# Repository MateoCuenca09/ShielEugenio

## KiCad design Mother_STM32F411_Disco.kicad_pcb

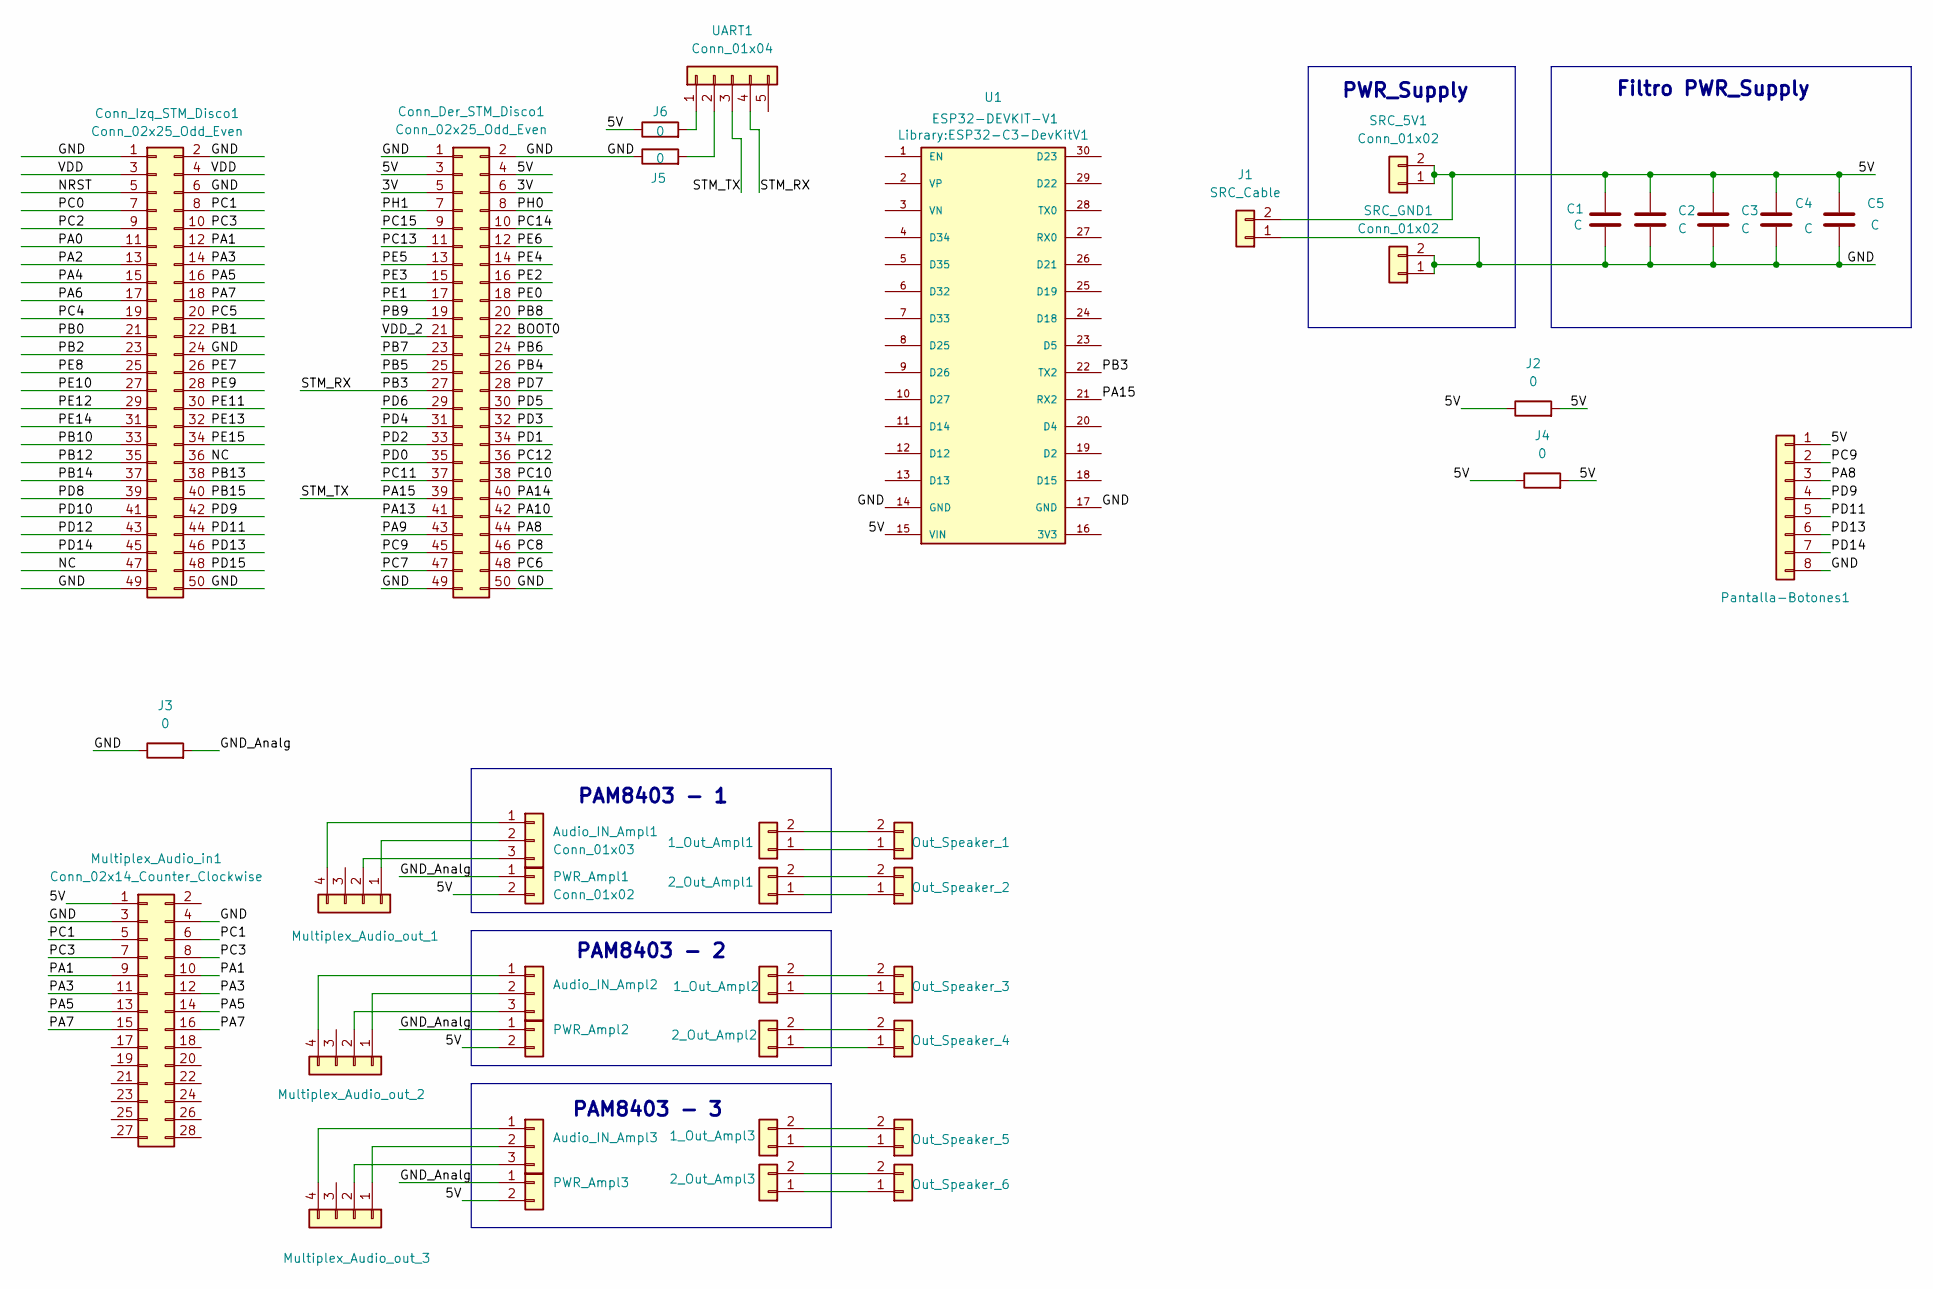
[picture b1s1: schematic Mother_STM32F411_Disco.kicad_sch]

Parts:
1_Out_Ampl1, 1_Out_Ampl2, 1_Out_Ampl3, 2_Out_Ampl1, 2_Out_Ampl2, 2_Out_Ampl3: Conn_01x02; PinSocket_1x02_P2.54mm_Vertical
Audio_IN_Ampl1, Audio_IN_Ampl2, Audio_IN_Ampl3: Conn_01x03; PinSocket_1x03_P2.54mm_Vertical
C1, C5: C; CP_Radial_D13.0mm_P5.00mm
C2, C3, C4: C; C_Disc_D8.0mm_W5.0mm_P5.00mm
Conn_Der_STM_Disco1: Conn_02x25_Odd_Even; PinSocket_2x25_P2.54mm_Vertical
Conn_Izq_STM_Disco1: Conn_02x25_Odd_Even; PinSocket_2x25_P2.54mm_Vertical
J1: SRC_Cable; TerminalBlock_Phoenix_MKDS-1,5-2_1x02_P5.00mm_Horizontal
J2, J3, J4, J5, J6: 0; R_1210_3225Metric_Pad1.30x2.65mm_HandSolder
Multiplex_Audio_in1: Conn_02x14_Counter_Clockwise; PinHeader_2x14_P2.54mm_Vertical
Multiplex_Audio_out_1, Multiplex_Audio_out_2, Multiplex_Audio_out_3: Conn_01x04; PinSocket_1x04_P2.54mm_Vertical
Out_Speaker_1, Out_Speaker_2, Out_Speaker_3, Out_Speaker_4, Out_Speaker_5, Out_Speaker_6: Conn_01x02; PinHeader_1x02_P2.54mm_Horizontal
PWR_Ampl1, PWR_Ampl2, PWR_Ampl3: Conn_01x02; PinSocket_1x02_P2.54mm_Vertical
Pantalla-Botones1: Conn_01x08; PinHeader_1x08_P2.54mm_Horizontal
SRC_5V1: Conn_01x02; PinSocket_1x02_P2.54mm_Vertical
SRC_GND1: Conn_01x02; PinSocket_1x02_P2.54mm_Vertical
U1: ESP32-DEVKIT-V1; ESP32-C3-DevKitV1; PARTREV N/A
UART1: Conn_01x04; PinHeader_1x05_P2.54mm_Horizontal

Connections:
/3V: Conn_Der_STM_Disco1.5, Conn_Der_STM_Disco1.6
/5V: C1.1, C2.1, C3.1, C4.1, C5.1, Conn_Der_STM_Disco1.3, Conn_Der_STM_Disco1.4, J1.2, J2.1, J2.2, J4.1, J4.2, J6.1, J6.2, Multiplex_Audio_in1.1, PWR_Ampl1.2, PWR_Ampl2.2, PWR_Ampl3.2, Pantalla-Botones1.1, SRC_5V1.1, SRC_5V1.2, U1.15 (VIN), UART1.1
/BOOT0: Conn_Der_STM_Disco1.22
/GND: C1.2, C2.2, C3.2, C4.2, C5.2, Conn_Der_STM_Disco1.1, Conn_Der_STM_Disco1.2, Conn_Der_STM_Disco1.49, Conn_Der_STM_Disco1.50, Conn_Izq_STM_Disco1.1, Conn_Izq_STM_Disco1.2, Conn_Izq_STM_Disco1.6, Conn_Izq_STM_Disco1.24, Conn_Izq_STM_Disco1.49, Conn_Izq_STM_Disco1.50, J1.1, J3.1, J5.1, Multiplex_Audio_in1.3, Multiplex_Audio_in1.4, Pantalla-Botones1.8, SRC_GND1.1, SRC_GND1.2, U1.14 (GND), U1.17 (GND)
/GND_Analg: J3.2, PWR_Ampl1.1, PWR_Ampl2.1, PWR_Ampl3.1
/NC: Conn_Izq_STM_Disco1.36, Conn_Izq_STM_Disco1.47
/NRST: Conn_Izq_STM_Disco1.5
/PA0: Conn_Izq_STM_Disco1.11
/PA1: Conn_Izq_STM_Disco1.12, Multiplex_Audio_in1.9, Multiplex_Audio_in1.10
/PA2: Conn_Izq_STM_Disco1.13
/PA3: Conn_Izq_STM_Disco1.14, Multiplex_Audio_in1.11, Multiplex_Audio_in1.12
/PA4: Conn_Izq_STM_Disco1.15
/PA5: Conn_Izq_STM_Disco1.16, Multiplex_Audio_in1.13, Multiplex_Audio_in1.14
/PA6: Conn_Izq_STM_Disco1.17
/PA7: Conn_Izq_STM_Disco1.18, Multiplex_Audio_in1.15, Multiplex_Audio_in1.16
/PA8: Conn_Der_STM_Disco1.44, Pantalla-Botones1.3
/PA9: Conn_Der_STM_Disco1.43
/PA10: Conn_Der_STM_Disco1.42
/PA13: Conn_Der_STM_Disco1.41
/PA14: Conn_Der_STM_Disco1.40
/PA15: Conn_Der_STM_Disco1.39, U1.21 (RX2), UART1.3
/PB0: Conn_Izq_STM_Disco1.21
/PB1: Conn_Izq_STM_Disco1.22
/PB2: Conn_Izq_STM_Disco1.23
/PB3: Conn_Der_STM_Disco1.27, U1.22 (TX2), UART1.4
/PB4: Conn_Der_STM_Disco1.26
/PB5: Conn_Der_STM_Disco1.25
/PB6: Conn_Der_STM_Disco1.24
/PB7: Conn_Der_STM_Disco1.23
/PB8: Conn_Der_STM_Disco1.20
/PB9: Conn_Der_STM_Disco1.19
/PB10: Conn_Izq_STM_Disco1.33
/PB12: Conn_Izq_STM_Disco1.35
/PB13: Conn_Izq_STM_Disco1.38
/PB14: Conn_Izq_STM_Disco1.37
/PB15: Conn_Izq_STM_Disco1.40
/PC0: Conn_Izq_STM_Disco1.7
/PC1: Conn_Izq_STM_Disco1.8, Multiplex_Audio_in1.5, Multiplex_Audio_in1.6
/PC2: Conn_Izq_STM_Disco1.9
/PC3: Conn_Izq_STM_Disco1.10, Multiplex_Audio_in1.7, Multiplex_Audio_in1.8
/PC4: Conn_Izq_STM_Disco1.19
/PC5: Conn_Izq_STM_Disco1.20
/PC6: Conn_Der_STM_Disco1.48
/PC7: Conn_Der_STM_Disco1.47
/PC8: Conn_Der_STM_Disco1.46
/PC9: Conn_Der_STM_Disco1.45, Pantalla-Botones1.2
/PC10: Conn_Der_STM_Disco1.38
/PC11: Conn_Der_STM_Disco1.37
/PC12: Conn_Der_STM_Disco1.36
/PC13: Conn_Der_STM_Disco1.11
/PC14: Conn_Der_STM_Disco1.10
/PC15: Conn_Der_STM_Disco1.9
/PD0: Conn_Der_STM_Disco1.35
/PD1: Conn_Der_STM_Disco1.34
/PD2: Conn_Der_STM_Disco1.33
/PD3: Conn_Der_STM_Disco1.32
/PD4: Conn_Der_STM_Disco1.31
/PD5: Conn_Der_STM_Disco1.30
/PD6: Conn_Der_STM_Disco1.29
/PD7: Conn_Der_STM_Disco1.28
/PD8: Conn_Izq_STM_Disco1.39
/PD9: Conn_Izq_STM_Disco1.42, Pantalla-Botones1.4
/PD10: Conn_Izq_STM_Disco1.41
/PD11: Conn_Izq_STM_Disco1.44, Pantalla-Botones1.5
/PD12: Conn_Izq_STM_Disco1.43
/PD13: Conn_Izq_STM_Disco1.46, Pantalla-Botones1.6
/PD14: Conn_Izq_STM_Disco1.45, Pantalla-Botones1.7
/PD15: Conn_Izq_STM_Disco1.48
/PE0: Conn_Der_STM_Disco1.18
/PE1: Conn_Der_STM_Disco1.17
/PE2: Conn_Der_STM_Disco1.16
/PE3: Conn_Der_STM_Disco1.15
/PE4: Conn_Der_STM_Disco1.14
/PE5: Conn_Der_STM_Disco1.13
/PE6: Conn_Der_STM_Disco1.12
/PE7: Conn_Izq_STM_Disco1.26
/PE8: Conn_Izq_STM_Disco1.25
/PE9: Conn_Izq_STM_Disco1.28
/PE10: Conn_Izq_STM_Disco1.27
/PE11: Conn_Izq_STM_Disco1.30
/PE12: Conn_Izq_STM_Disco1.29
/PE13: Conn_Izq_STM_Disco1.32
/PE14: Conn_Izq_STM_Disco1.31
/PE15: Conn_Izq_STM_Disco1.34
/PH0: Conn_Der_STM_Disco1.8
/PH1: Conn_Der_STM_Disco1.7
/VDD: Conn_Izq_STM_Disco1.3, Conn_Izq_STM_Disco1.4
/VDD_2: Conn_Der_STM_Disco1.21
unnamed: 1_Out_Ampl1.1, Out_Speaker_1.1
unnamed: 1_Out_Ampl1.2, Out_Speaker_1.2
unnamed: 1_Out_Ampl2.1, Out_Speaker_3.1
unnamed: 1_Out_Ampl2.2, Out_Speaker_3.2
unnamed: 1_Out_Ampl3.1, Out_Speaker_5.1
unnamed: 1_Out_Ampl3.2, Out_Speaker_5.2
unnamed: 2_Out_Ampl1.1, Out_Speaker_2.1
unnamed: 2_Out_Ampl1.2, Out_Speaker_2.2
unnamed: 2_Out_Ampl2.1, Out_Speaker_4.1
unnamed: 2_Out_Ampl2.2, Out_Speaker_4.2
unnamed: 2_Out_Ampl3.1, Out_Speaker_6.1
unnamed: 2_Out_Ampl3.2, Out_Speaker_6.2
unnamed: Audio_IN_Ampl1.1, Multiplex_Audio_out_1.4
unnamed: Audio_IN_Ampl1.2, Multiplex_Audio_out_1.1
unnamed: Audio_IN_Ampl1.3, Multiplex_Audio_out_1.2
unnamed: Audio_IN_Ampl2.1, Multiplex_Audio_out_2.4
unnamed: Audio_IN_Ampl2.2, Multiplex_Audio_out_2.1
unnamed: Audio_IN_Ampl2.3, Multiplex_Audio_out_2.2
unnamed: Audio_IN_Ampl3.1, Multiplex_Audio_out_3.4
unnamed: Audio_IN_Ampl3.2, Multiplex_Audio_out_3.1
unnamed: Audio_IN_Ampl3.3, Multiplex_Audio_out_3.2
unnamed: J5.2, UART1.2

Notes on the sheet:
PWR_Supply
PAM8403 - 3
Filtro PWR_Supply
PAM8403 - 1
PAM8403 - 2

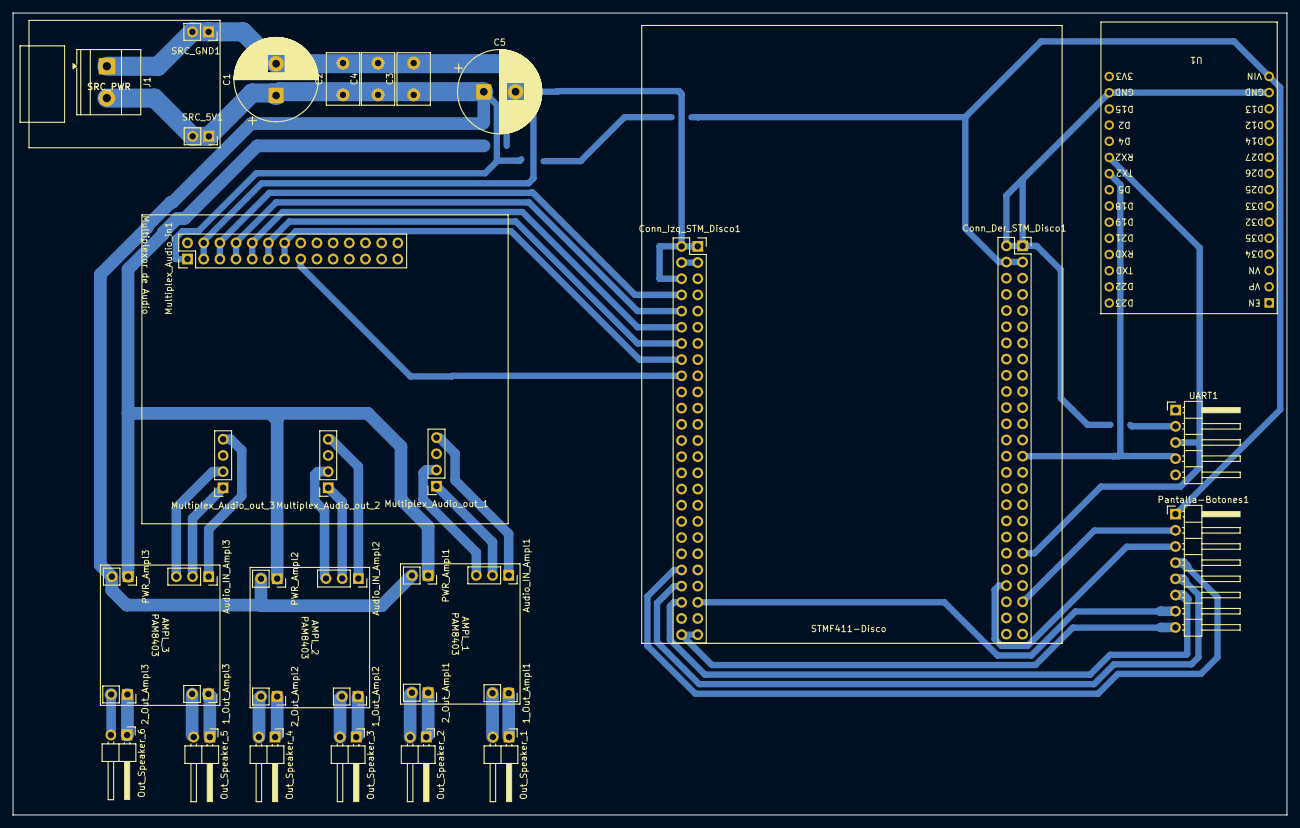
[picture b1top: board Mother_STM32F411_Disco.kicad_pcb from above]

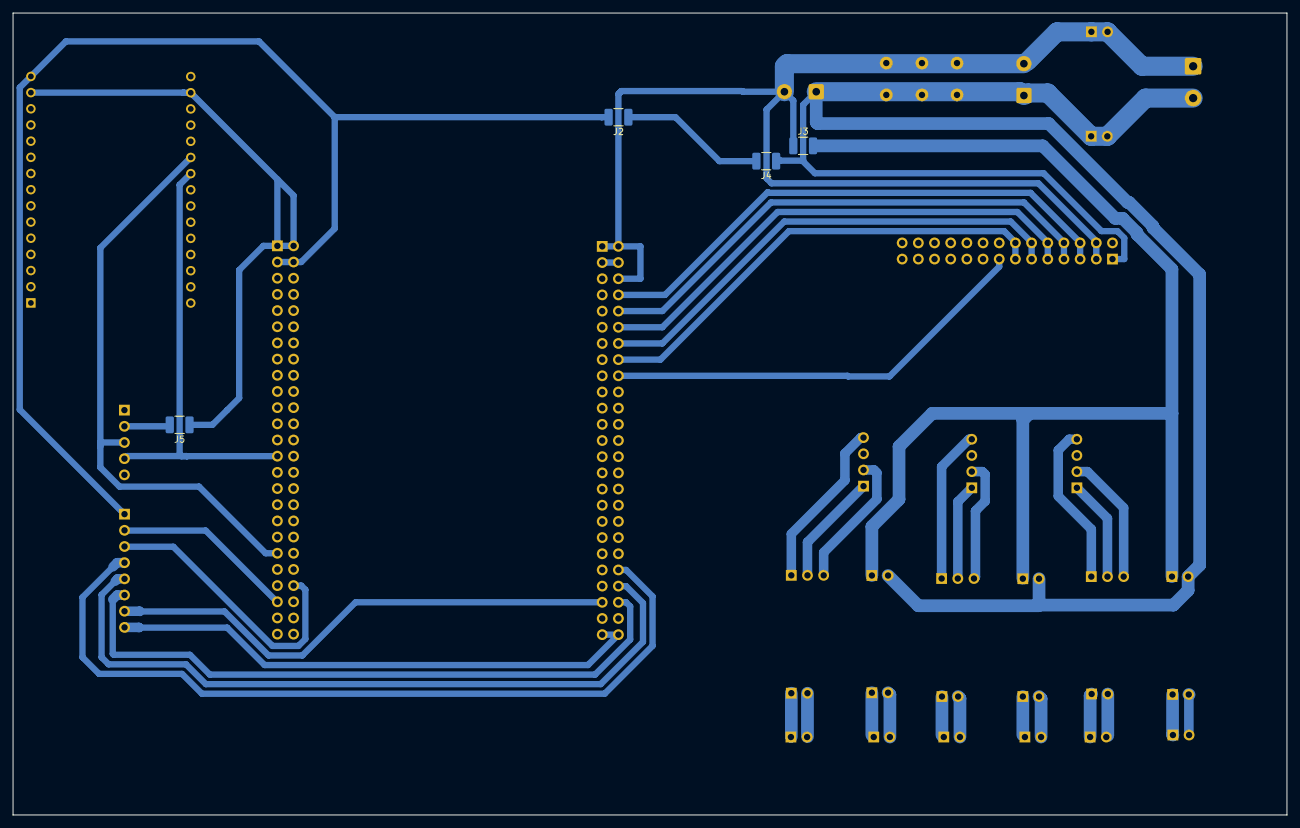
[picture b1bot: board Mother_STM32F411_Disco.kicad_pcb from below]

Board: 2 copper layers, 200.0 x 125.9 mm, 39 parts (4 on the bottom side), 42 nets.

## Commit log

2025-05-08 inicializando repo
2025-05-27 boceteando todavia
2025-05-29 SA-18: placa de esp32 devkitv1 agregada a el esquematico
2025-06-02 Mudamos librerias a local de proyecto y asignamos 3d models nuevamente
2025-06-02 .sch mergeado
2025-06-02 UART STM conectada
2025-06-03 Huellas agregadas, src_pwr agregado
2025-06-04 SA'18: agregue pistas de la ESP32 y actualice el footprint
2025-06-04 SA-18: Actualice el simbolo del esp32 para que sea mas congruente con la huella
2025-06-04 ni idea que cambio
2025-06-06 Huellas placas check, falta huellas filtros
2025-06-06 fixed tamaño placa SRC_Supply
2025-06-11 Placa lista para ser routeada con pistas
2025-06-11 acomodando pines de la placa stm
2025-06-11 PCB layout preliminar
2025-06-12 Huellas OK, PCB layout OK
2025-06-12 PCB version 2
